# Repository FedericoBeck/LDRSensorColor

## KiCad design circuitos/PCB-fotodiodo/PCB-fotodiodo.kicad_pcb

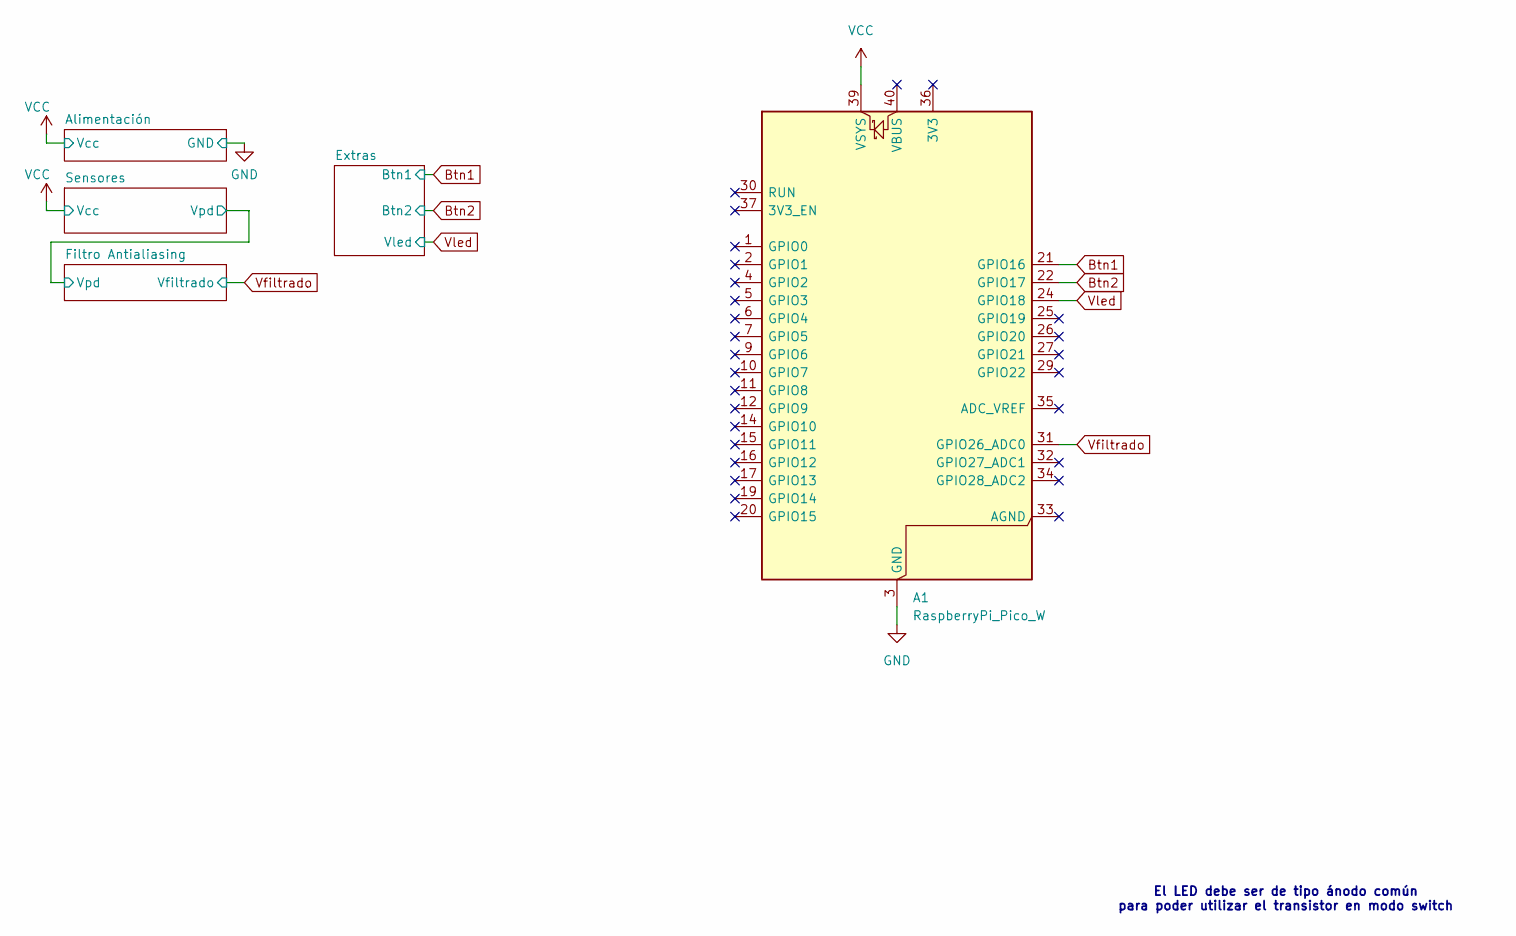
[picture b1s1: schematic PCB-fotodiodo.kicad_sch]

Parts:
A1: RaspberryPi_Pico_W; RaspberryPi_Pico_Common_THT

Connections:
Btn1: A1.21 (GPIO16); also elsewhere on the board
Btn2: A1.22 (GPIO17); also elsewhere on the board
GND: A1.3 (GND), A1.8 (GND), A1.13 (GND), A1.18 (GND), A1.23 (GND), A1.28 (GND), A1.38 (GND); also elsewhere on the board
VCC: A1.39 (VSYS); also elsewhere on the board
Vfiltrado: A1.31 (GPIO26_ADC0); also elsewhere on the board
Vled: A1.24 (GPIO18); also elsewhere on the board

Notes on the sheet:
El LED debe ser de tipo ánodo común para poder utilizar el transistor en modo switch

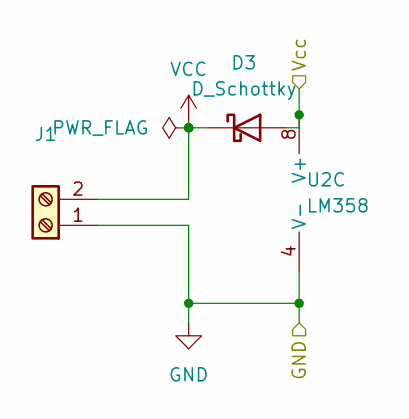
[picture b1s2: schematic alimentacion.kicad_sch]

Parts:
D3: D_Schottky; D_DO-41_SOD81_P5.08mm_Vertical_AnodeUp
J1: TerminalBlock_bornier-2_P5.08mm
U2: LM358

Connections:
GND: J1.1, U2.4 (V-); also elsewhere on the board
VCC: D3.1 (K), D3.2 (A), J1.2, U2.8 (V+); also elsewhere on the board

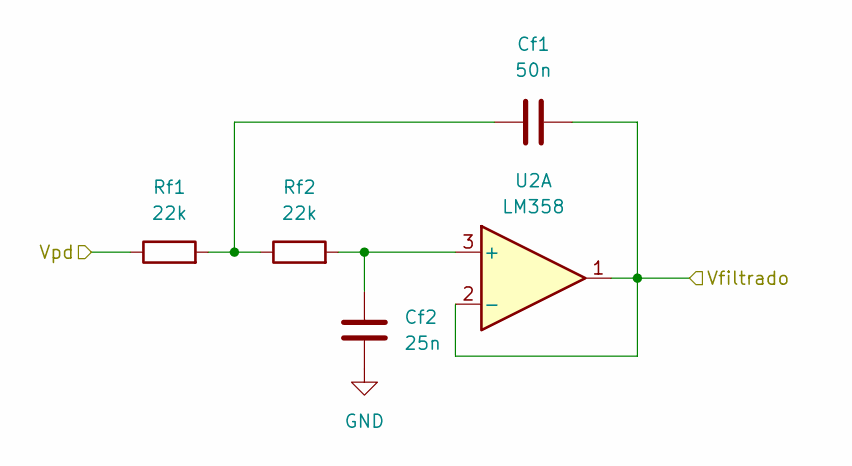
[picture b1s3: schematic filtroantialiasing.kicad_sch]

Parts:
Cf1: 50n; C_Disc_D5.0mm_W2.5mm_P5.00mm
Cf2: 25n; C_Disc_D5.0mm_W2.5mm_P5.00mm
Rf1, Rf2: 22k; R_Axial_DIN0207_L6.3mm_D2.5mm_P7.62mm_Horizontal
U2: LM358

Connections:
/Filtro Antialiasing/Vpd: Rf1.1; also elsewhere on the board
GND: Cf2.2; also elsewhere on the board
unnamed: Cf1.2, Rf1.2, Rf2.1
unnamed: Cf2.1, Rf2.2, U2.3 (+)
Vfiltrado: Cf1.1, U2.1, U2.2 (-); also elsewhere on the board

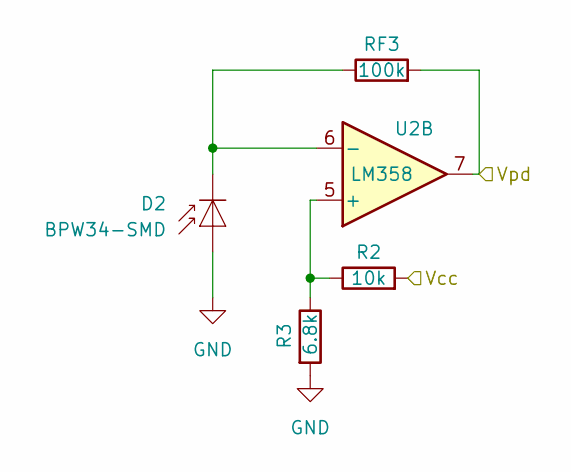
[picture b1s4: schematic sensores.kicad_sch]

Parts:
D2: BPW34-SMD; Osram_BPW34S-SMD
R2: 10k; R_Axial_DIN0207_L6.3mm_D2.5mm_P7.62mm_Horizontal
R3: 6.8k; R_Axial_DIN0207_L6.3mm_D2.5mm_P7.62mm_Horizontal
RF3: 100k; R_Axial_DIN0207_L6.3mm_D2.5mm_P7.62mm_Horizontal
U2: LM358

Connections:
/Filtro Antialiasing/Vpd: RF3.2, U2.7; also elsewhere on the board
GND: D2.2 (A), R3.2; also elsewhere on the board
unnamed: D2.1 (K), RF3.1, U2.6 (-)
unnamed: R2.1, R3.1, U2.5 (+)
VCC: R2.2; also elsewhere on the board

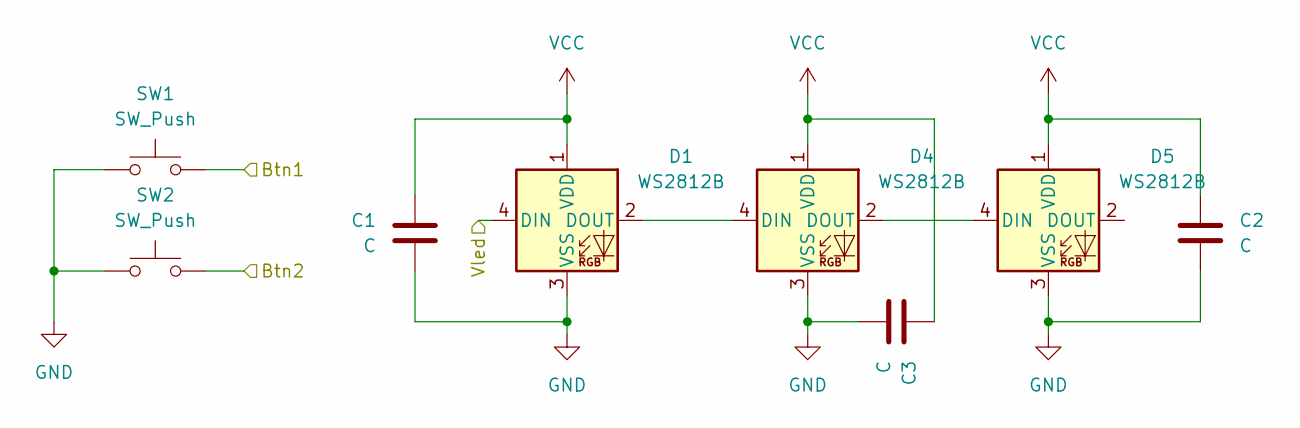
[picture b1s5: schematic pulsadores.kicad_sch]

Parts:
C1, C2, C3: C; D_T-1_P5.08mm_Horizontal
D1, D4, D5: WS2812B; LED_WS2812B-Mini_PLCC4_3.5x3.5mm
SW1, SW2: SW_Push; SW_PUSH-12mm

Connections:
Btn1: SW1.2; also elsewhere on the board
Btn2: SW2.2; also elsewhere on the board
GND: C1.2, C2.2, C3.2, D1.3 (VSS), D4.3 (VSS), D5.3 (VSS), SW1.1, SW2.1; also elsewhere on the board
unnamed: D1.2 (DOUT), D4.4 (DIN)
unnamed: D4.2 (DOUT), D5.4 (DIN)
VCC: C1.1, C2.1, C3.1, D1.1 (VDD), D4.1 (VDD), D5.1 (VDD); also elsewhere on the board
Vled: D1.4 (DIN); also elsewhere on the board

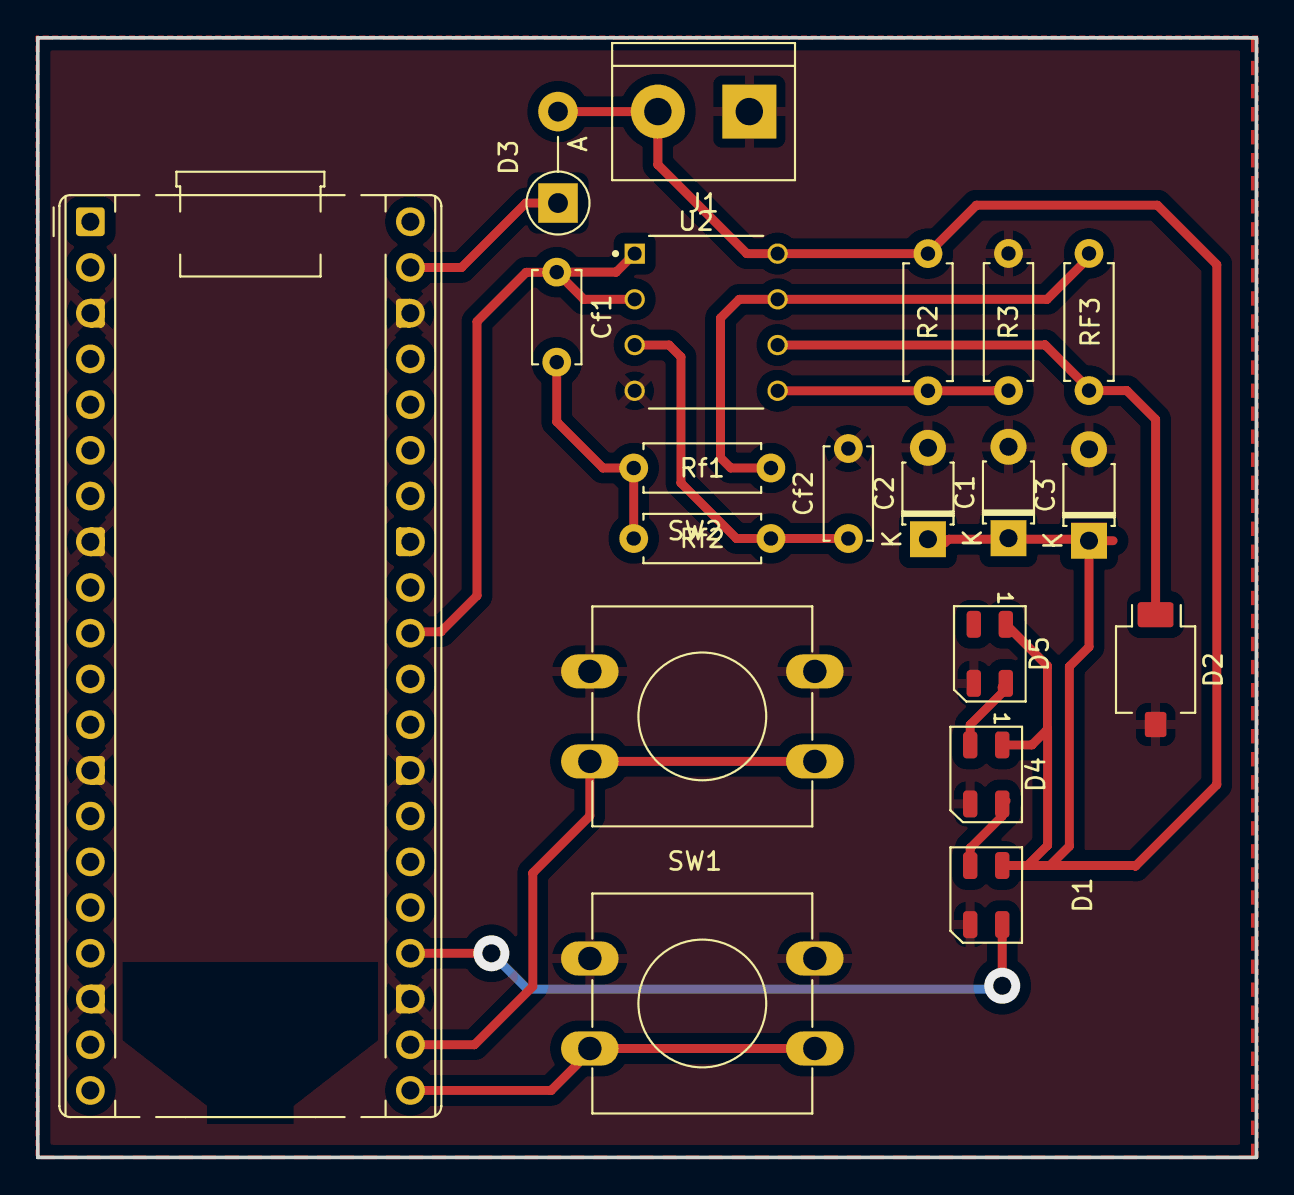
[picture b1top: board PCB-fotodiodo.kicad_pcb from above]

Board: 2 copper layers, 67.7 x 62.2 mm, 20 parts (0 on the bottom side), 13 nets.

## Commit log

2025-04-27 PCB fotodiodo
2025-04-28 fixed cmake - should compile
